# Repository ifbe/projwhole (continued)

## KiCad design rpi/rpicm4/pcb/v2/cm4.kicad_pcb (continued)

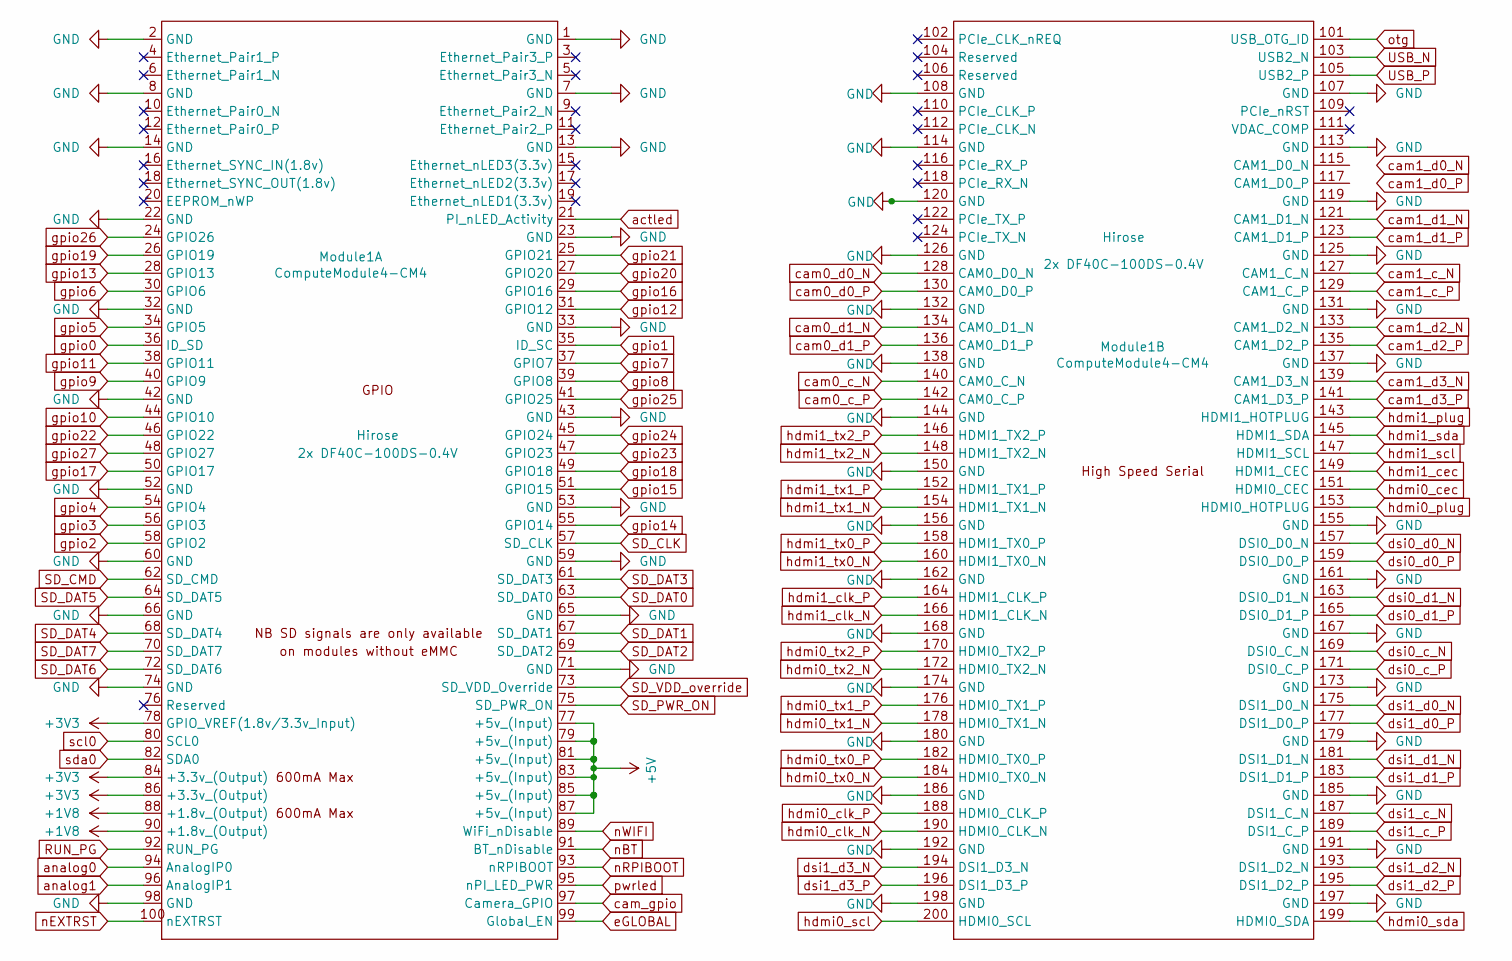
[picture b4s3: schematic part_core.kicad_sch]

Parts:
Module1: ComputeModule4-CM4; Raspberry-Pi-4-Compute-Module

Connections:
+1V8: Module1.88 (+1.8v_(Output)), Module1.90 (+1.8v_(Output)); also elsewhere on the board
+3V3: Module1.78 (GPIO_VREF(1.8v/3.3v_Input)), Module1.84 (+3.3v_(Output)), Module1.86 (+3.3v_(Output)); also elsewhere on the board
+5V: Module1.77 (+5v_(Input)), Module1.79 (+5v_(Input)), Module1.81 (+5v_(Input)), Module1.83 (+5v_(Input)), Module1.85 (+5v_(Input)), Module1.87 (+5v_(Input)); also elsewhere on the board
GND: Module1.1 (GND), Module1.2 (GND), Module1.7 (GND), Module1.8 (GND), Module1.13 (GND), Module1.14 (GND), Module1.22 (GND), Module1.23 (GND), Module1.32 (GND), Module1.33 (GND), Module1.42 (GND), Module1.43 (GND), Module1.52 (GND), Module1.53 (GND), Module1.59 (GND), Module1.60 (GND), Module1.65 (GND), Module1.66 (GND), Module1.71 (GND), Module1.74 (GND), Module1.98 (GND), Module1.107 (GND), Module1.108 (GND), Module1.113 (GND), Module1.114 (GND), Module1.119 (GND), Module1.120 (GND), Module1.125 (GND), Module1.126 (GND), Module1.131 (GND), Module1.132 (GND), Module1.137 (GND), Module1.138 (GND), Module1.144 (GND), Module1.150 (GND), Module1.155 (GND), Module1.156 (GND), Module1.161 (GND), Module1.162 (GND), Module1.167 (GND), Module1.168 (GND), Module1.173 (GND), Module1.174 (GND), Module1.179 (GND), Module1.180 (GND), Module1.185 (GND), Module1.186 (GND), Module1.191 (GND), Module1.192 (GND), Module1.197 (GND), Module1.198 (GND); also elsewhere on the board
RUN_PG: Module1.92 (RUN_PG)
SD_CLK: Module1.57 (SD_CLK); also elsewhere on the board
SD_CMD: Module1.62 (SD_CMD); also elsewhere on the board
SD_DAT0: Module1.63 (SD_DAT0); also elsewhere on the board
SD_DAT1: Module1.67 (SD_DAT1); also elsewhere on the board
SD_DAT2: Module1.69 (SD_DAT2); also elsewhere on the board
SD_DAT3: Module1.61 (SD_DAT3); also elsewhere on the board
SD_DAT4: Module1.68 (SD_DAT4)
SD_DAT5: Module1.64 (SD_DAT5)
SD_DAT6: Module1.72 (SD_DAT6)
SD_DAT7: Module1.70 (SD_DAT7)
SD_PWR_ON: Module1.75 (SD_PWR_ON)
SD_VDD_override: Module1.73 (SD_VDD_Override)
USB_N: Module1.103 (USB2_N); also elsewhere on the board
USB_P: Module1.105 (USB2_P); also elsewhere on the board
actled: Module1.21 (PI_nLED_Activity); also elsewhere on the board
analog0: Module1.94 (AnalogIP0); also elsewhere on the board
analog1: Module1.96 (AnalogIP1); also elsewhere on the board
cam0_c_N: Module1.140 (CAM0_C_N); also elsewhere on the board
cam0_c_P: Module1.142 (CAM0_C_P); also elsewhere on the board
cam0_d0_N: Module1.128 (CAM0_D0_N); also elsewhere on the board
cam0_d0_P: Module1.130 (CAM0_D0_P); also elsewhere on the board
cam0_d1_N: Module1.134 (CAM0_D1_N); also elsewhere on the board
cam0_d1_P: Module1.136 (CAM0_D1_P); also elsewhere on the board
cam1_c_N: Module1.127 (CAM1_C_N); also elsewhere on the board
cam1_c_P: Module1.129 (CAM1_C_P); also elsewhere on the board
cam1_d1_N: Module1.121 (CAM1_D1_N); also elsewhere on the board
cam1_d1_P: Module1.123 (CAM1_D1_P); also elsewhere on the board
cam1_d2_N: Module1.133 (CAM1_D2_N); also elsewhere on the board
cam1_d2_P: Module1.135 (CAM1_D2_P); also elsewhere on the board
cam1_d3_N: Module1.139 (CAM1_D3_N); also elsewhere on the board
cam1_d3_P: Module1.141 (CAM1_D3_P); also elsewhere on the board
cam_gpio: Module1.97 (Camera_GPIO); also elsewhere on the board
dsi0_c_N: Module1.169 (DSI0_C_N); also elsewhere on the board
dsi0_c_P: Module1.171 (DSI0_C_P); also elsewhere on the board
dsi0_d0_N: Module1.157 (DSI0_D0_N); also elsewhere on the board
dsi0_d0_P: Module1.159 (DSI0_D0_P); also elsewhere on the board
dsi0_d1_N: Module1.163 (DSI0_D1_N); also elsewhere on the board
dsi0_d1_P: Module1.165 (DSI0_D1_P); also elsewhere on the board
dsi1_c_N: Module1.187 (DSI1_C_N); also elsewhere on the board
dsi1_c_P: Module1.189 (DSI1_C_P); also elsewhere on the board
dsi1_d0_N: Module1.175 (DSI1_D0_N); also elsewhere on the board
dsi1_d0_P: Module1.177 (DSI1_D0_P); also elsewhere on the board
dsi1_d1_N: Module1.181 (DSI1_D1_N); also elsewhere on the board
dsi1_d1_P: Module1.183 (DSI1_D1_P); also elsewhere on the board
dsi1_d2_N: Module1.193 (DSI1_D2_N); also elsewhere on the board
dsi1_d2_P: Module1.195 (DSI1_D2_P); also elsewhere on the board
dsi1_d3_N: Module1.194 (DSI1_D3_N); also elsewhere on the board
dsi1_d3_P: Module1.196 (DSI1_D3_P); also elsewhere on the board
eGLOBAL: Module1.99 (Global_EN); also elsewhere on the board
gpio0: Module1.36 (ID_SD); also elsewhere on the board
gpio1: Module1.35 (ID_SC); also elsewhere on the board
gpio2: Module1.58 (GPIO2); also elsewhere on the board
gpio3: Module1.56 (GPIO3); also elsewhere on the board
gpio4: Module1.54 (GPIO4); also elsewhere on the board
gpio5: Module1.34 (GPIO5); also elsewhere on the board
gpio6: Module1.30 (GPIO6); also elsewhere on the board
gpio7: Module1.37 (GPIO7); also elsewhere on the board
gpio8: Module1.39 (GPIO8); also elsewhere on the board
gpio9: Module1.40 (GPIO9); also elsewhere on the board
gpio10: Module1.44 (GPIO10); also elsewhere on the board
gpio11: Module1.38 (GPIO11); also elsewhere on the board
gpio12: Module1.31 (GPIO12); also elsewhere on the board
gpio13: Module1.28 (GPIO13); also elsewhere on the board
gpio14: Module1.55 (GPIO14); also elsewhere on the board
gpio15: Module1.51 (GPIO15); also elsewhere on the board
gpio16: Module1.29 (GPIO16); also elsewhere on the board
gpio17: Module1.50 (GPIO17); also elsewhere on the board
gpio18: Module1.49 (GPIO18); also elsewhere on the board
gpio19: Module1.26 (GPIO19); also elsewhere on the board
gpio20: Module1.27 (GPIO20); also elsewhere on the board
gpio21: Module1.25 (GPIO21); also elsewhere on the board
gpio22: Module1.46 (GPIO22); also elsewhere on the board
gpio23: Module1.47 (GPIO23); also elsewhere on the board
gpio24: Module1.45 (GPIO24); also elsewhere on the board
gpio25: Module1.41 (GPIO25); also elsewhere on the board
gpio26: Module1.24 (GPIO26); also elsewhere on the board
gpio27: Module1.48 (GPIO27); also elsewhere on the board
hdmi0_cec: Module1.151 (HDMI0_CEC); also elsewhere on the board
hdmi0_clk_N: Module1.190 (HDMI0_CLK_N); also elsewhere on the board
hdmi0_clk_P: Module1.188 (HDMI0_CLK_P); also elsewhere on the board
hdmi0_plug: Module1.153 (HDMI0_HOTPLUG); also elsewhere on the board
hdmi0_scl: Module1.200 (HDMI0_SCL); also elsewhere on the board
hdmi0_sda: Module1.199 (HDMI0_SDA); also elsewhere on the board
hdmi0_tx0_N: Module1.184 (HDMI0_TX0_N); also elsewhere on the board
hdmi0_tx0_P: Module1.182 (HDMI0_TX0_P); also elsewhere on the board
hdmi0_tx1_N: Module1.178 (HDMI0_TX1_N); also elsewhere on the board
hdmi0_tx1_P: Module1.176 (HDMI0_TX1_P); also elsewhere on the board
hdmi0_tx2_N: Module1.172 (HDMI0_TX2_N); also elsewhere on the board
hdmi0_tx2_P: Module1.170 (HDMI0_TX2_P); also elsewhere on the board
hdmi1_cec: Module1.149 (HDMI1_CEC); also elsewhere on the board
hdmi1_clk_N: Module1.166 (HDMI1_CLK_N); also elsewhere on the board
hdmi1_clk_P: Module1.164 (HDMI1_CLK_P); also elsewhere on the board
hdmi1_plug: Module1.143 (HDMI1_HOTPLUG); also elsewhere on the board
hdmi1_scl: Module1.147 (HDMI1_SCL); also elsewhere on the board
hdmi1_sda: Module1.145 (HDMI1_SDA); also elsewhere on the board
hdmi1_tx0_N: Module1.160 (HDMI1_TX0_N); also elsewhere on the board
hdmi1_tx0_P: Module1.158 (HDMI1_TX0_P); also elsewhere on the board
hdmi1_tx1_N: Module1.154 (HDMI1_TX1_N); also elsewhere on the board
hdmi1_tx1_P: Module1.152 (HDMI1_TX1_P); also elsewhere on the board
hdmi1_tx2_N: Module1.148 (HDMI1_TX2_N); also elsewhere on the board
hdmi1_tx2_P: Module1.146 (HDMI1_TX2_P); also elsewhere on the board
nBT: Module1.91 (BT_nDisable)
nEXTRST: Module1.100 (nEXTRST)
nRPIBOOT: Module1.93 (nRPIBOOT); also elsewhere on the board
nWIFI: Module1.89 (WiFi_nDisable)
otg: Module1.101 (USB_OTG_ID); also elsewhere on the board
pwrled: Module1.95 (nPI_LED_PWR); also elsewhere on the board
scl0: Module1.80 (SCL0); also elsewhere on the board
sda0: Module1.82 (SDA0); also elsewhere on the board

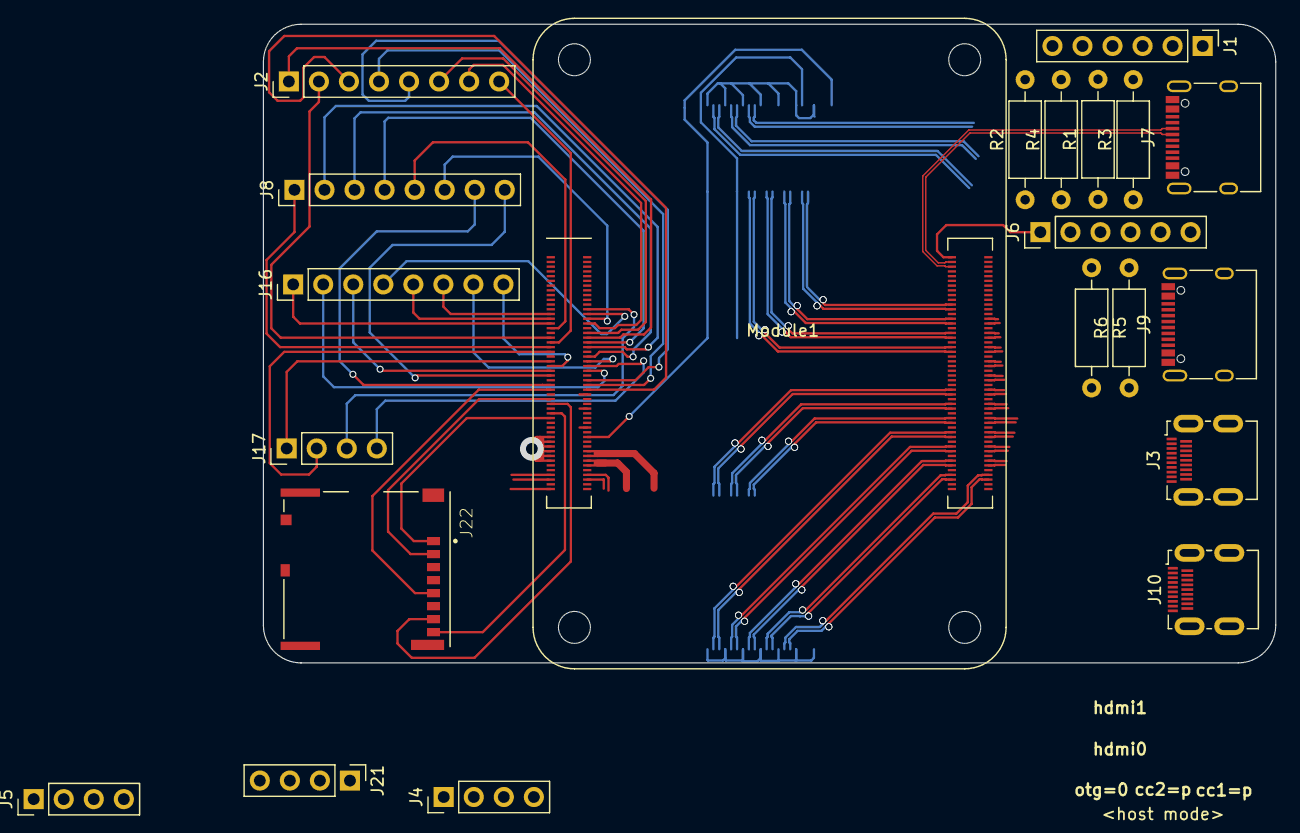
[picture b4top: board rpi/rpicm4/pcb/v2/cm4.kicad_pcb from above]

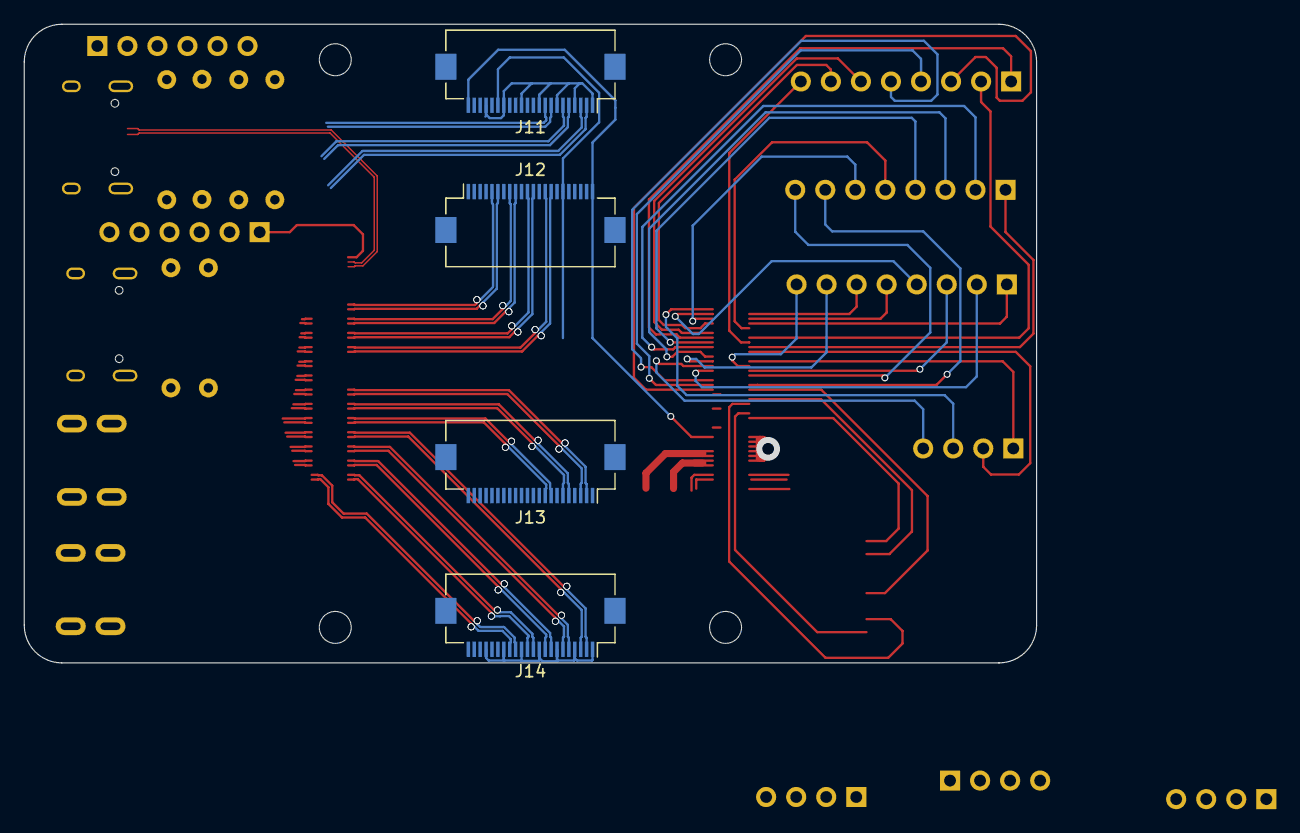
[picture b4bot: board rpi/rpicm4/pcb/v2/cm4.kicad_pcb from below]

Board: 2 copper layers, 85.6 x 54.0 mm, 25 parts (4 on the bottom side), 114 nets.

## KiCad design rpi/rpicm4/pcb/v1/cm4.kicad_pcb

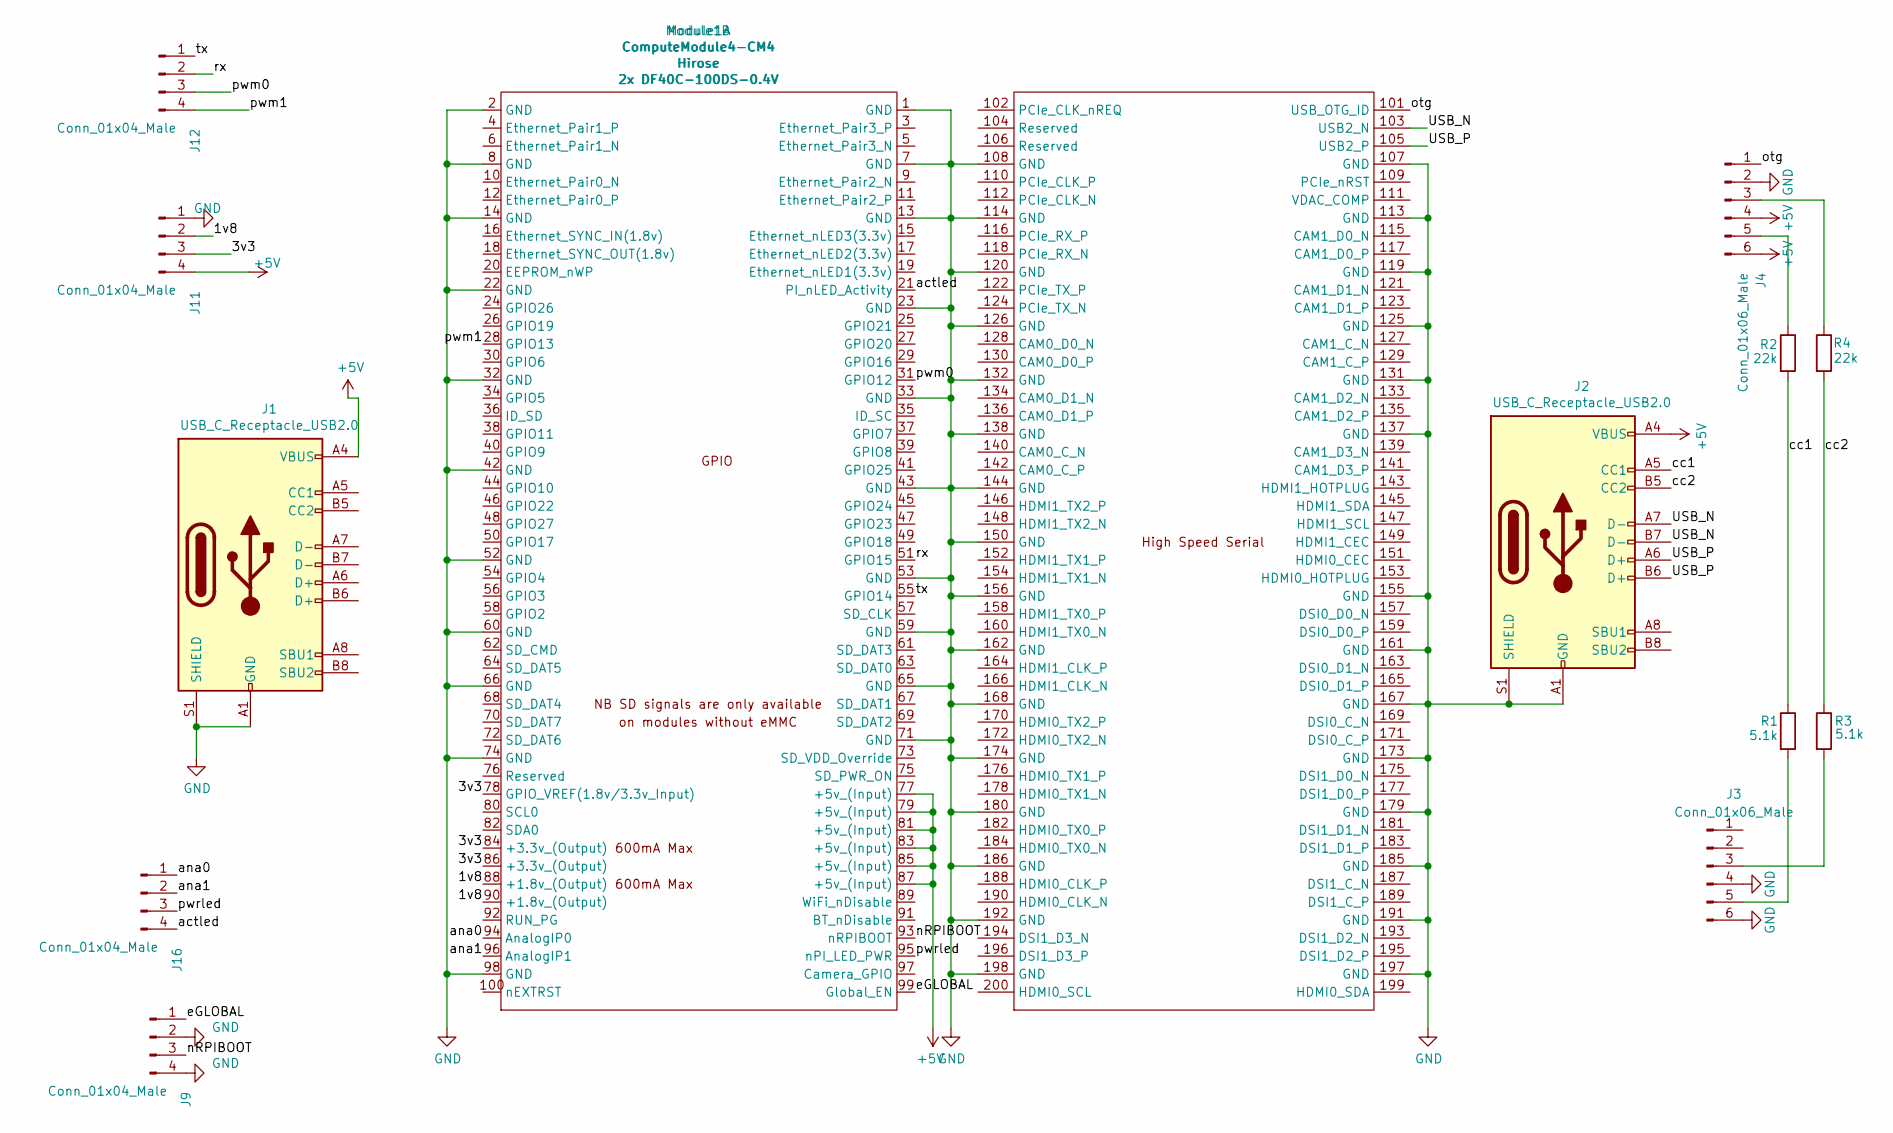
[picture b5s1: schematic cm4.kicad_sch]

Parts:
J1, J2: USB_C_Receptacle_USB2.0; USB_C_Receptacle_XKB_U262-16XN-4BVC11
J3, J4: Conn_01x06_Male; PinHeader_1x06_P2.54mm_Vertical
J9, J11, J12, J16: Conn_01x04_Male; PinHeader_1x04_P2.54mm_Vertical
Module1: ComputeModule4-CM4; Raspberry-Pi-4-Compute-Module
R1, R3: 5.1k; R_Axial_DIN0207_L6.3mm_D2.5mm_P10.16mm_Horizontal
R2, R4: 22k; R_Axial_DIN0207_L6.3mm_D2.5mm_P10.16mm_Horizontal

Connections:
+5V: J1.A4 (VBUS), J1.A9 (VBUS), J1.B4 (VBUS), J1.B9 (VBUS), J2.A4 (VBUS), J2.A9 (VBUS), J2.B4 (VBUS), J2.B9 (VBUS), J4.4, J4.6, J11.4, Module1.77 (+5v_(Input)), Module1.79 (+5v_(Input)), Module1.81 (+5v_(Input)), Module1.83 (+5v_(Input)), Module1.85 (+5v_(Input)), Module1.87 (+5v_(Input))
/1v8: J11.2, Module1.88 (+1.8v_(Output)), Module1.90 (+1.8v_(Output))
/3v3: J11.3, Module1.78 (GPIO_VREF(1.8v/3.3v_Input)), Module1.84 (+3.3v_(Output)), Module1.86 (+3.3v_(Output))
/USB_N: J2.A7 (D-), J2.B7 (D-), Module1.103 (USB2_N)
/USB_P: J2.A6 (D+), J2.B6 (D+), Module1.105 (USB2_P)
/actled: J16.4, Module1.21 (PI_nLED_Activity)
/ana0: J16.1, Module1.94 (AnalogIP0)
/ana1: J16.2, Module1.96 (AnalogIP1)
/cc1: J2.A5 (CC1), R1.1, R2.2
/cc2: J2.B5 (CC2), R3.1, R4.2
/eGLOBAL: J9.1, Module1.99 (Global_EN)
/nRPIBOOT: J9.3, Module1.93 (nRPIBOOT)
/otg: J4.1, Module1.101 (USB_OTG_ID)
/pwm0: J12.3, Module1.31 (GPIO12)
/pwm1: J12.4, Module1.28 (GPIO13)
/pwrled: J16.3, Module1.95 (nPI_LED_PWR)
/rx: J12.2, Module1.51 (GPIO15)
/tx: J12.1, Module1.55 (GPIO14)
GND: J1.A1 (GND), J1.A12 (GND), J1.B1 (GND), J1.B12 (GND), J1.S1 (SHIELD), J2.A1 (GND), J2.A12 (GND), J2.B1 (GND), J2.B12 (GND), J2.S1 (SHIELD), J3.4, J3.6, J4.2, J9.2, J9.4, J11.1, Module1.1 (GND), Module1.2 (GND), Module1.7 (GND), Module1.8 (GND), Module1.13 (GND), Module1.14 (GND), Module1.22 (GND), Module1.23 (GND), Module1.32 (GND), Module1.33 (GND), Module1.42 (GND), Module1.43 (GND), Module1.52 (GND), Module1.53 (GND), Module1.59 (GND), Module1.60 (GND), Module1.65 (GND), Module1.66 (GND), Module1.71 (GND), Module1.74 (GND), Module1.98 (GND), Module1.107 (GND), Module1.108 (GND), Module1.113 (GND), Module1.114 (GND), Module1.119 (GND), Module1.120 (GND), Module1.125 (GND), Module1.126 (GND), Module1.131 (GND), Module1.132 (GND), Module1.137 (GND), Module1.138 (GND), Module1.144 (GND), Module1.150 (GND), Module1.155 (GND), Module1.156 (GND), Module1.161 (GND), Module1.162 (GND), Module1.167 (GND), Module1.168 (GND), Module1.173 (GND), Module1.174 (GND), Module1.179 (GND), Module1.180 (GND), Module1.185 (GND), Module1.186 (GND), Module1.191 (GND), Module1.192 (GND), Module1.197 (GND), Module1.198 (GND)
unnamed: J3.5, R1.2
unnamed: J4.5, R2.1
unnamed: J3.3, R3.2
unnamed: J4.3, R4.1

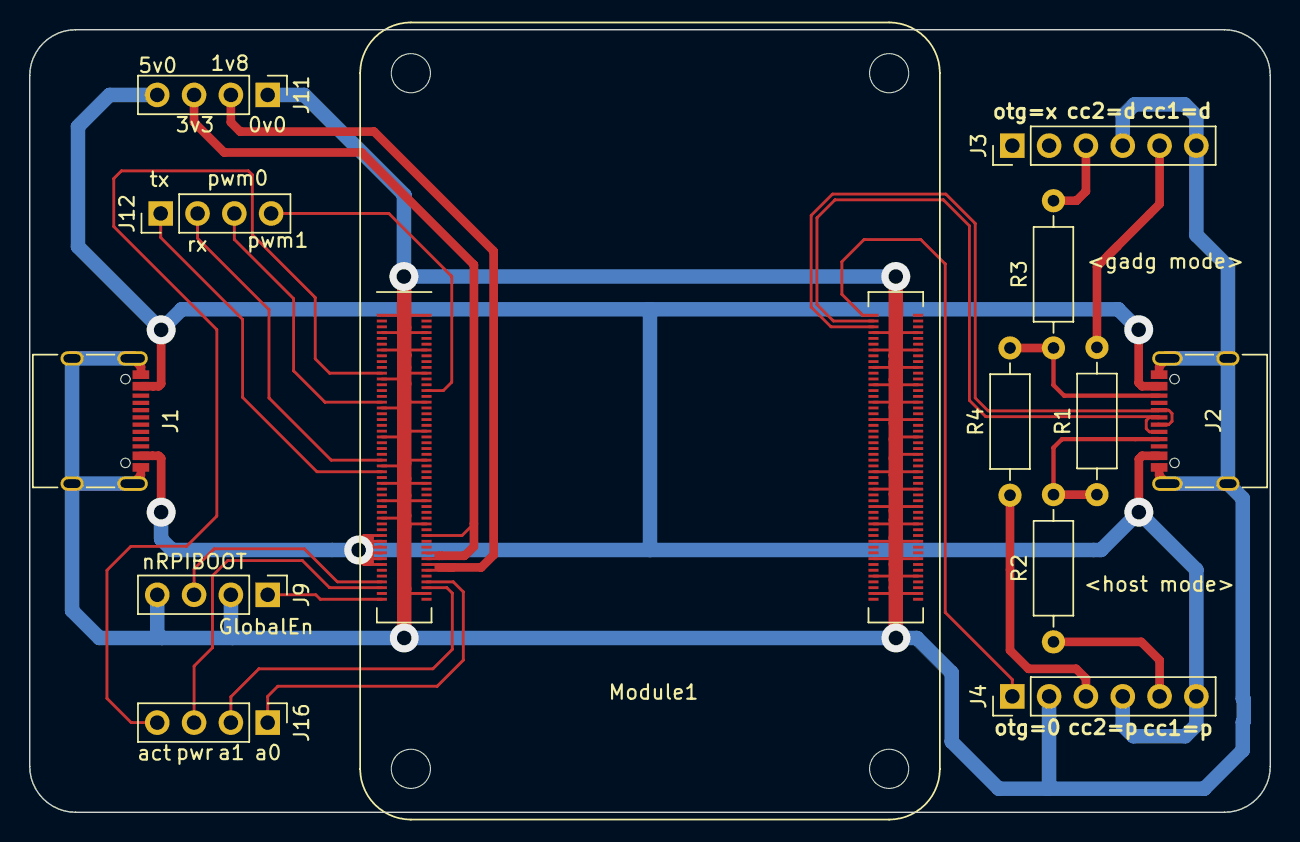
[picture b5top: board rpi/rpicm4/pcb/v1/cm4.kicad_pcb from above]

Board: 2 copper layers, 85.6 x 54.0 mm, 13 parts (0 on the bottom side), 23 nets.

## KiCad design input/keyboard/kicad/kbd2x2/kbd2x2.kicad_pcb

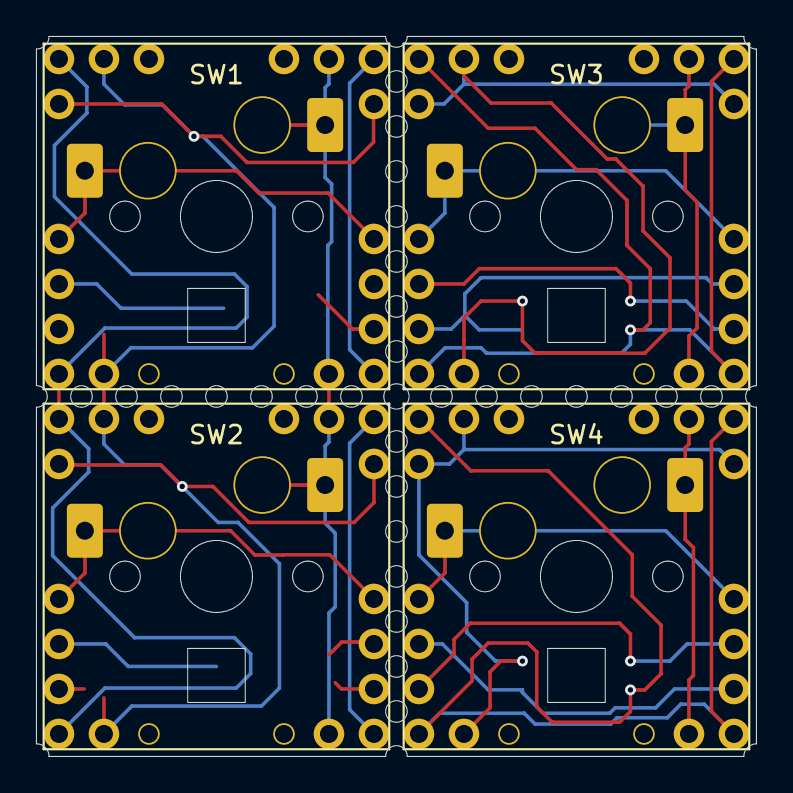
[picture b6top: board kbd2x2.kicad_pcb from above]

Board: 2 copper layers, 40.0 x 40.0 mm, 4 parts (0 on the bottom side), 6 nets.

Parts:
SW1, SW3: mykbd; seat_ltor
SW2, SW4: mykbd; seat_rtol

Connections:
GND: SW1.6, SW2.6, SW3.6, SW4.6
unnamed: SW1.1, SW3.1
unnamed: SW1.2, SW2.2
unnamed: SW2.1, SW4.1
unnamed: SW3.2, SW4.2
VCC: SW1.5, SW2.5, SW3.5, SW4.5

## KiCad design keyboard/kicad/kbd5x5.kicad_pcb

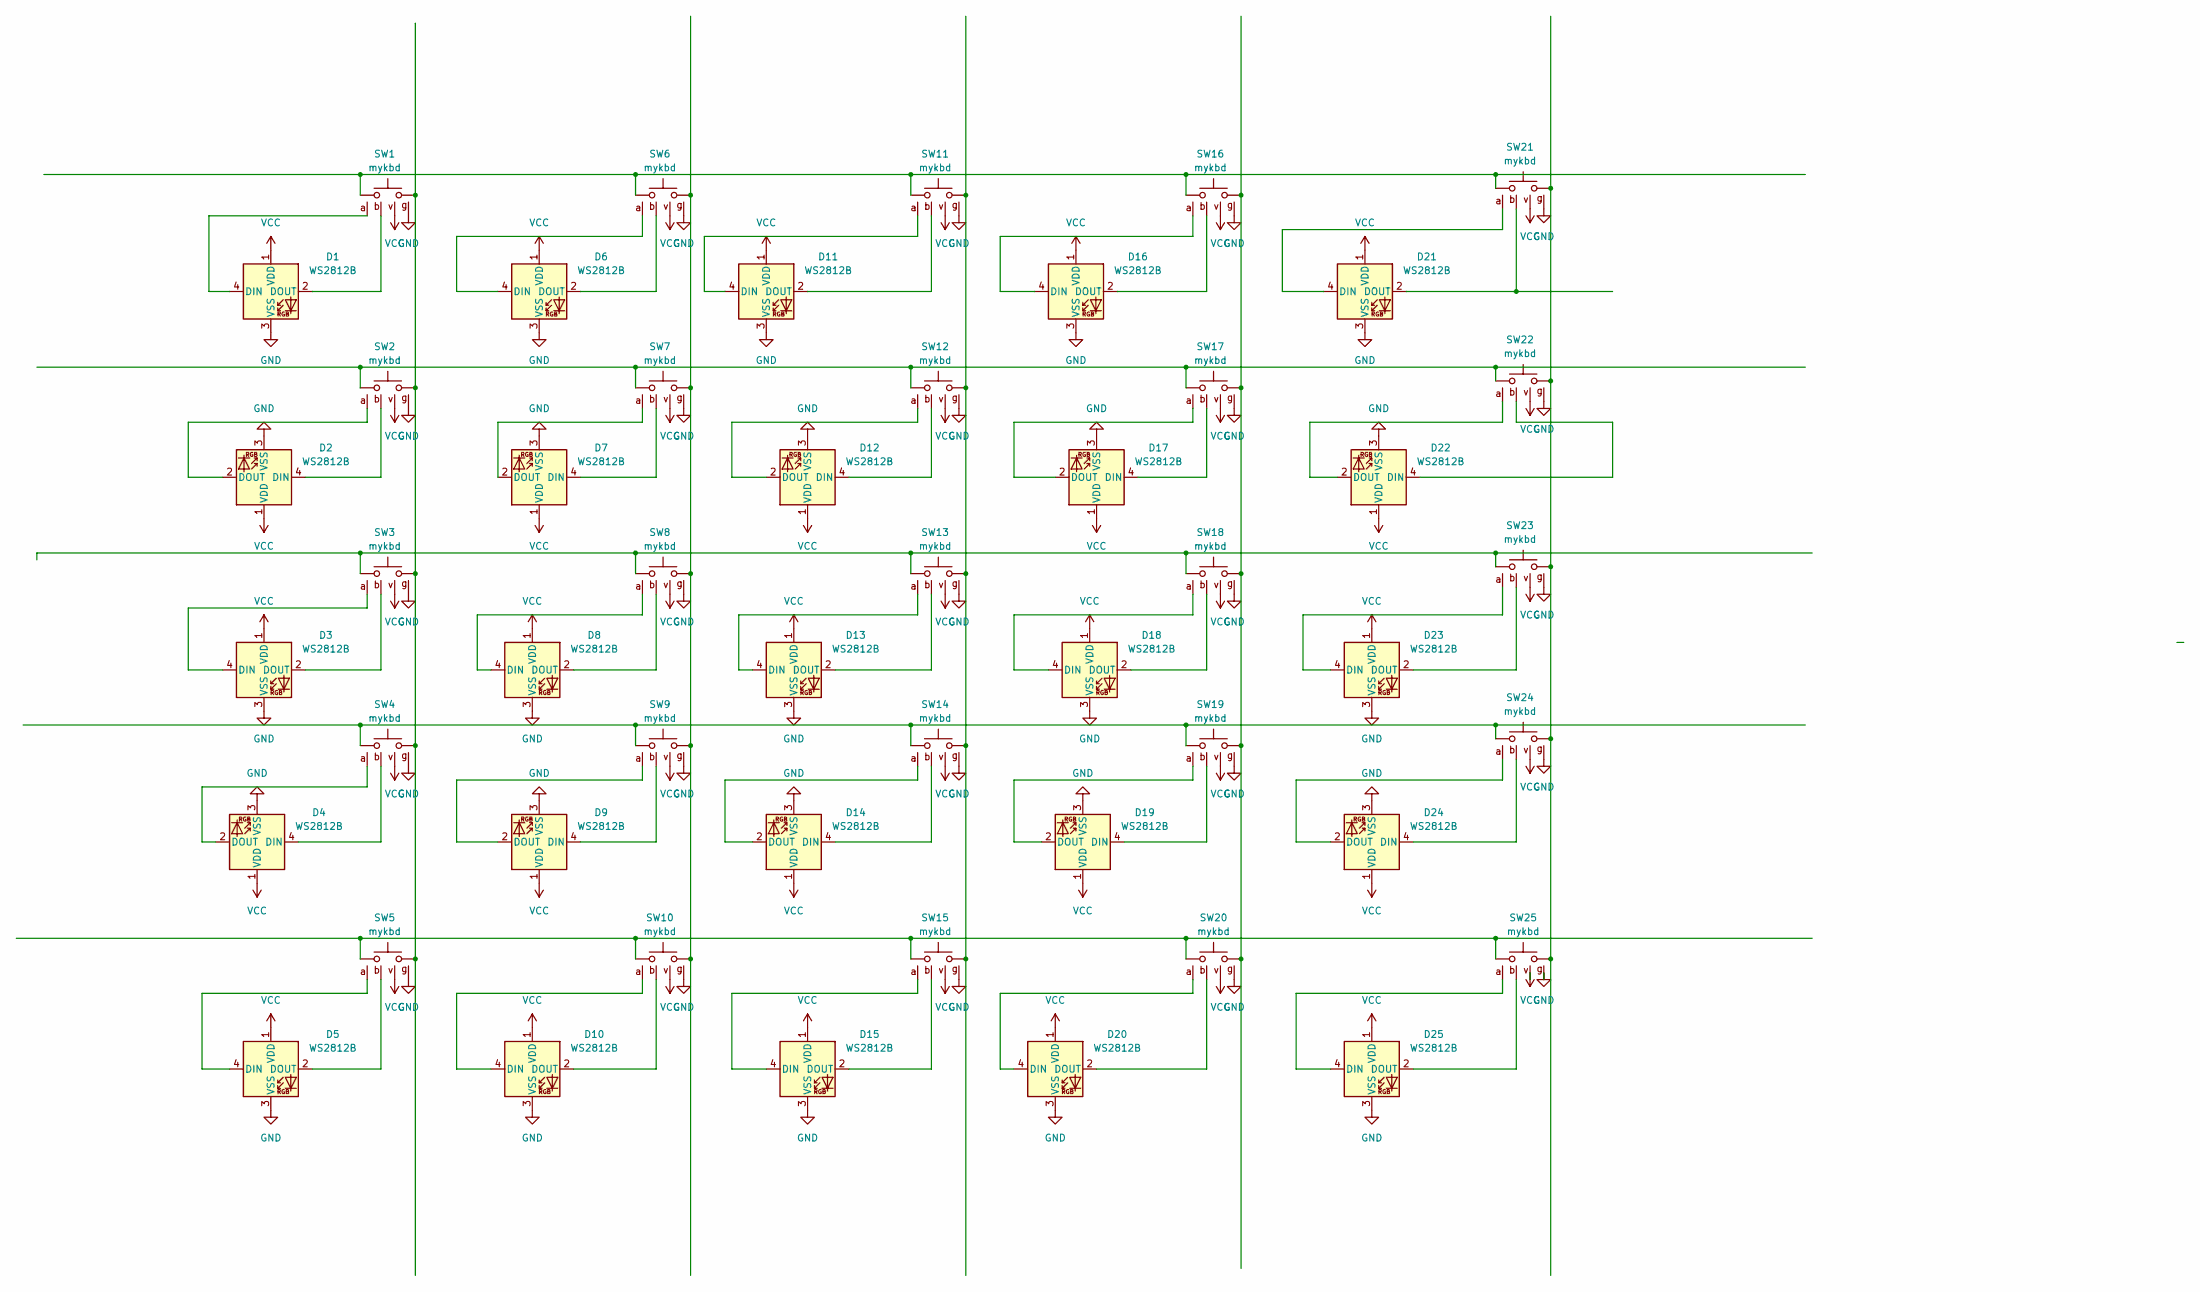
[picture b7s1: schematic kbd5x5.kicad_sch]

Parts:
D1, D2, D3, D4, D5, D6, D7, D8, D9, D10, D11, D12, D13, D14, D15, D16, D17, D18, D19, D20, D21, D22, D23, D24, D25: WS2812B; LED_WS2812B_PLCC4_5.0x5.0mm_P3.2mm
SW1, SW2, SW3, SW4, SW5, SW6, SW7, SW8, SW9, SW10, SW11, SW12, SW13, SW14, SW15, SW16, SW17, SW18, SW19, SW20, SW21, SW22, SW23, SW24, SW25: mykbd; seat

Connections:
GND: D1.3 (VSS), D2.3 (VSS), D3.3 (VSS), D4.3 (VSS), D5.3 (VSS), D6.3 (VSS), D7.3 (VSS), D8.3 (VSS), D9.3 (VSS), D10.3 (VSS), D11.3 (VSS), D12.3 (VSS), D13.3 (VSS), D14.3 (VSS), D15.3 (VSS), D16.3 (VSS), D17.3 (VSS), D18.3 (VSS), D19.3 (VSS), D20.3 (VSS), D21.3 (VSS), D22.3 (VSS), D23.3 (VSS), D24.3 (VSS), D25.3 (VSS), SW1.6, SW2.6, SW3.6, SW4.6, SW5.6, SW6.6, SW7.6, SW8.6, SW9.6, SW10.6, SW11.6, SW12.6, SW13.6, SW14.6, SW15.6, SW16.6, SW17.6, SW18.6, SW19.6, SW20.6, SW21.6, SW22.6, SW23.6, SW24.6, SW25.6
unnamed: D1.4 (DIN), SW1.3
unnamed: D1.2 (DOUT), SW1.4
unnamed: D2.4 (DIN), SW2.4
unnamed: D2.2 (DOUT), SW2.3
unnamed: D3.4 (DIN), SW3.3
unnamed: D3.2 (DOUT), SW3.4
unnamed: D4.4 (DIN), SW4.4
unnamed: D4.2 (DOUT), SW4.3
unnamed: D5.4 (DIN), SW5.3
unnamed: D5.2 (DOUT), SW5.4
unnamed: D6.4 (DIN), SW6.3
unnamed: D6.2 (DOUT), SW6.4
unnamed: D7.4 (DIN), SW7.4
unnamed: D7.2 (DOUT), SW7.3
unnamed: D8.4 (DIN), SW8.3
unnamed: D8.2 (DOUT), SW8.4
unnamed: D9.4 (DIN), SW9.4
unnamed: D9.2 (DOUT), SW9.3
unnamed: D10.4 (DIN), SW10.3
unnamed: D10.2 (DOUT), SW10.4
unnamed: D11.4 (DIN), SW11.3
unnamed: D11.2 (DOUT), SW11.4
unnamed: D12.4 (DIN), SW12.4
unnamed: D12.2 (DOUT), SW12.3
unnamed: D13.4 (DIN), SW13.3
unnamed: D13.2 (DOUT), SW13.4
unnamed: D14.4 (DIN), SW14.4
unnamed: D14.2 (DOUT), SW14.3
unnamed: D15.4 (DIN), SW15.3
unnamed: D15.2 (DOUT), SW15.4
unnamed: D16.4 (DIN), SW16.3
unnamed: D16.2 (DOUT), SW16.4
unnamed: D17.4 (DIN), SW17.4
unnamed: D17.2 (DOUT), SW17.3
unnamed: D18.4 (DIN), SW18.3
unnamed: D18.2 (DOUT), SW18.4
unnamed: D19.4 (DIN), SW19.4
unnamed: D19.2 (DOUT), SW19.3
unnamed: D20.4 (DIN), SW20.3
unnamed: D20.2 (DOUT), SW20.4
unnamed: D21.4 (DIN), SW21.3
unnamed: D21.2 (DOUT), SW21.4
unnamed: D22.4 (DIN), SW22.4
unnamed: D22.2 (DOUT), SW22.3
unnamed: D23.4 (DIN), SW23.3
unnamed: D23.2 (DOUT), SW23.4
unnamed: D24.4 (DIN), SW24.4
unnamed: D24.2 (DOUT), SW24.3
unnamed: D25.4 (DIN), SW25.3
unnamed: D25.2 (DOUT), SW25.4
unnamed: SW1.1, SW6.1, SW11.1, SW16.1, SW21.1
unnamed: SW1.2, SW2.2, SW3.2, SW4.2, SW5.2
unnamed: SW5.1, SW10.1, SW15.1, SW20.1, SW25.1
unnamed: SW6.2, SW7.2, SW8.2, SW9.2, SW10.2
unnamed: SW11.2, SW12.2, SW13.2, SW14.2, SW15.2
unnamed: SW2.1, SW7.1, SW12.1, SW17.1, SW22.1
unnamed: SW3.1, SW8.1, SW13.1, SW18.1, SW23.1
unnamed: SW4.1, SW9.1, SW14.1, SW19.1, SW24.1
unnamed: SW16.2, SW17.2, SW18.2, SW19.2, SW20.2
unnamed: SW21.2, SW22.2, SW23.2, SW24.2, SW25.2
VCC: D1.1 (VDD), D2.1 (VDD), D3.1 (VDD), D4.1 (VDD), D5.1 (VDD), D6.1 (VDD), D7.1 (VDD), D8.1 (VDD), D9.1 (VDD), D10.1 (VDD), D11.1 (VDD), D12.1 (VDD), D13.1 (VDD), D14.1 (VDD), D15.1 (VDD), D16.1 (VDD), D17.1 (VDD), D18.1 (VDD), D19.1 (VDD), D20.1 (VDD), D21.1 (VDD), D22.1 (VDD), D23.1 (VDD), D24.1 (VDD), D25.1 (VDD), SW1.5, SW2.5, SW3.5, SW4.5, SW5.5, SW6.5, SW7.5, SW8.5, SW9.5, SW10.5, SW11.5, SW12.5, SW13.5, SW14.5, SW15.5, SW16.5, SW17.5, SW18.5, SW19.5, SW20.5, SW21.5, SW22.5, SW23.5, SW24.5, SW25.5

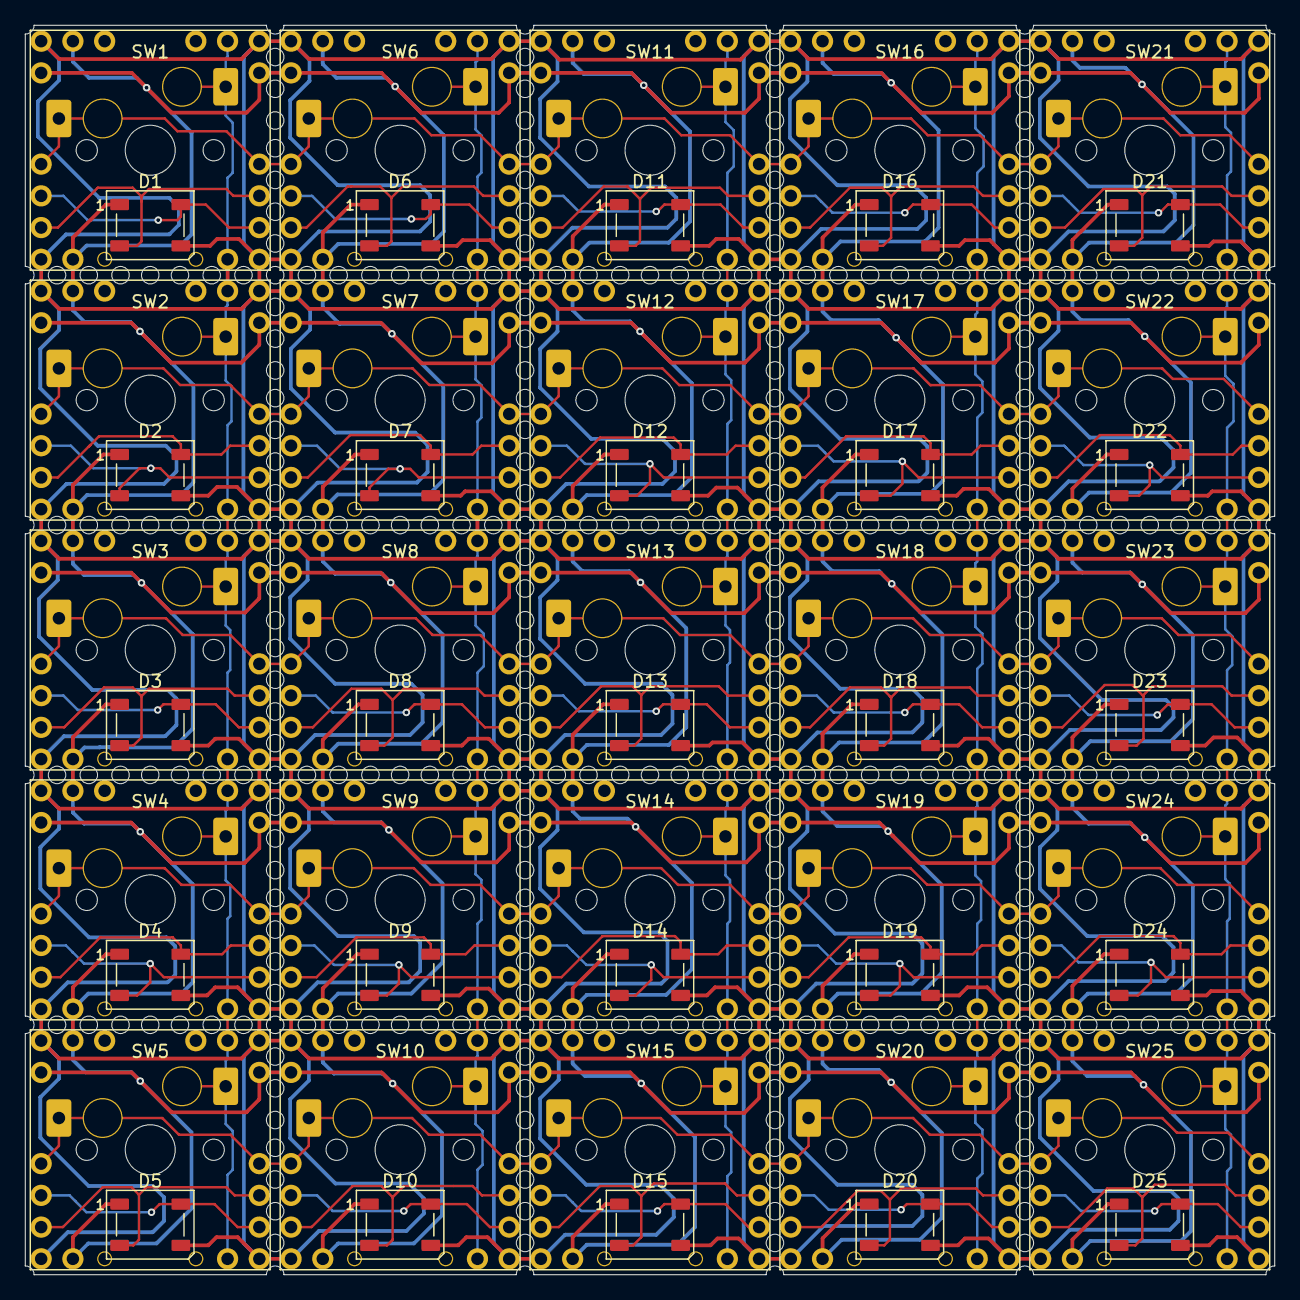
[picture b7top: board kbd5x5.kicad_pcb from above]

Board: 2 copper layers, 100.0 x 100.0 mm, 50 parts (0 on the bottom side), 62 nets.

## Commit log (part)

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2020-07-06 place holder
2020-07-11 balance/cad
2020-07-13 balance robot
2020-10-23 rpicm4 baseboard
2020-10-24 rpicm4
2020-10-24 rpicm4 usb
2020-10-24 rpicm4: typec ufp/dfp
2020-10-24 rpicm4: dwc2 host/device
2020-10-25 rpicm4: usb mode
2020-10-26 rpicm4: nRPIBOOT, UART, typec.cc
2020-10-27 rpicm4: led pwr/act,analog 0/1,pwm 0/1,uart tx/rx
2020-10-28 rpicm4: signal@front, power@back
2020-10-28 rpicm4: fix wire
2020-10-29 rpicm4: line width 1.0mm for vcc/gnd
2020-11-01 rpicm4: round corner, better layout
2020-11-02 rpicm4: better wiring
2020-11-02 rpicm4: better text
2020-11-11 kicad: balance,focesc,robotdog
2020-11-11 focesc: drv8305.symbol
2020-11-21 balance robot: power board
2020-11-25 balance robot: scaffold
2020-11-27 balance robot: frame.scad
2020-11-29 balance robot: cad,pcb
2023-05-07 more things
2023-09-07 some 3d model scad
2023-10-09 modify toycar.scad, reorganize directory
2023-10-10 vehicle: make board easier to print
2023-10-18 vehicle
2024-01-01 cammountabovetv, vehicle
2024-01-21 reorganize, add different vehicle
2025-01-12 recent changes
2025-01-13 esp32s3+mpu6050: mahony algo
2025-01-14 esp32+mpu6050: correct quaternion, seperate to different modules
2025-01-27 reorganize robot*
2025-01-28 two wheel balancing robot: esp32s3 add wifi and ble module
2025-02-01 two-wheel-balancing-robot: fix wifi log, modify 3d model
2025-02-04 two wheel balancing robot arduino code: battery and motor
2025-02-05 two wheel balancing robot: battery and pid
2025-02-07 balancingrobot: code-pid, 3d-esp32shield
2025-02-08 balancing robot: update mahony code, wait 200 iter before motor output
2025-02-09 balancing robot: wifi set mahony pid, modify 3d and pcb
2025-02-10 balancing robot: 1.change pid in web in wifi 2.power board 3.another logic board esp32s3_weact+icm42688
2025-02-11 balancing robot code: 1.choose logic board: esp32s3_muselab or esp32s3_weact 2.choose imu chip: mpu6050 or icm42688 3.choose motor: tt motor(drv8833) or stepper motor(drv8825)
2025-02-12 balancing robot: fix 3d model power part, add comment in battery code
2025-02-15 djiflip protect case and bms activebalancing
2025-02-16 balancing robot: prepare for stepper motor
2025-02-16 balancing robot: 3d model of drv8825 seat
2025-02-19 balancing robot stepper motor, dont use esp32s3 pin19,20(usb)
2025-02-23 balancing robot(stepper motor): update pwm in timer isr, pid param, and other minor change
2025-02-24 balancing robot: web adjust more param, better ttmotor and stepmotor control
2025-02-27 esp32s3 arduino: udp, bmi270, mpu9250
2025-03-04 battery/xxx, 6 leg robot, balancing robot, esp32-can
2025-03-29 esp32s3 test tool: can(twai)
2025-03-30 simple 6leg robot(cheap 9g servo version)
2025-03-30 esp32 can control xiaomi motor
2025-04-05 esp32s3 can, bambu h2d 2 material tray
2025-04-11 esp32s3 can: tbox debug tool now have 3 modes
2025-05-03 +keyboard
2025-05-03 xiaomi motor
2025-06-01 keyboard: pinout align with 2.54mm Perforated circuit board
2025-07-11 keyboard: esp32s3 arduino code
2025-07-11 balancing robot: dont while1() when imu not connected
2025-07-11 keyboard pcb: bottom board(esp32s3 minimal 20mmx40mm)
2025-07-11 keyboard scad update
2025-07-19 glass scad, keyboard case scad
2025-07-20 reorganize dir, keyboard pcb update
2025-08-01 improve: keyboard, 6leg, rpicm4
2025-08-15 input/keyboard: newest working version
